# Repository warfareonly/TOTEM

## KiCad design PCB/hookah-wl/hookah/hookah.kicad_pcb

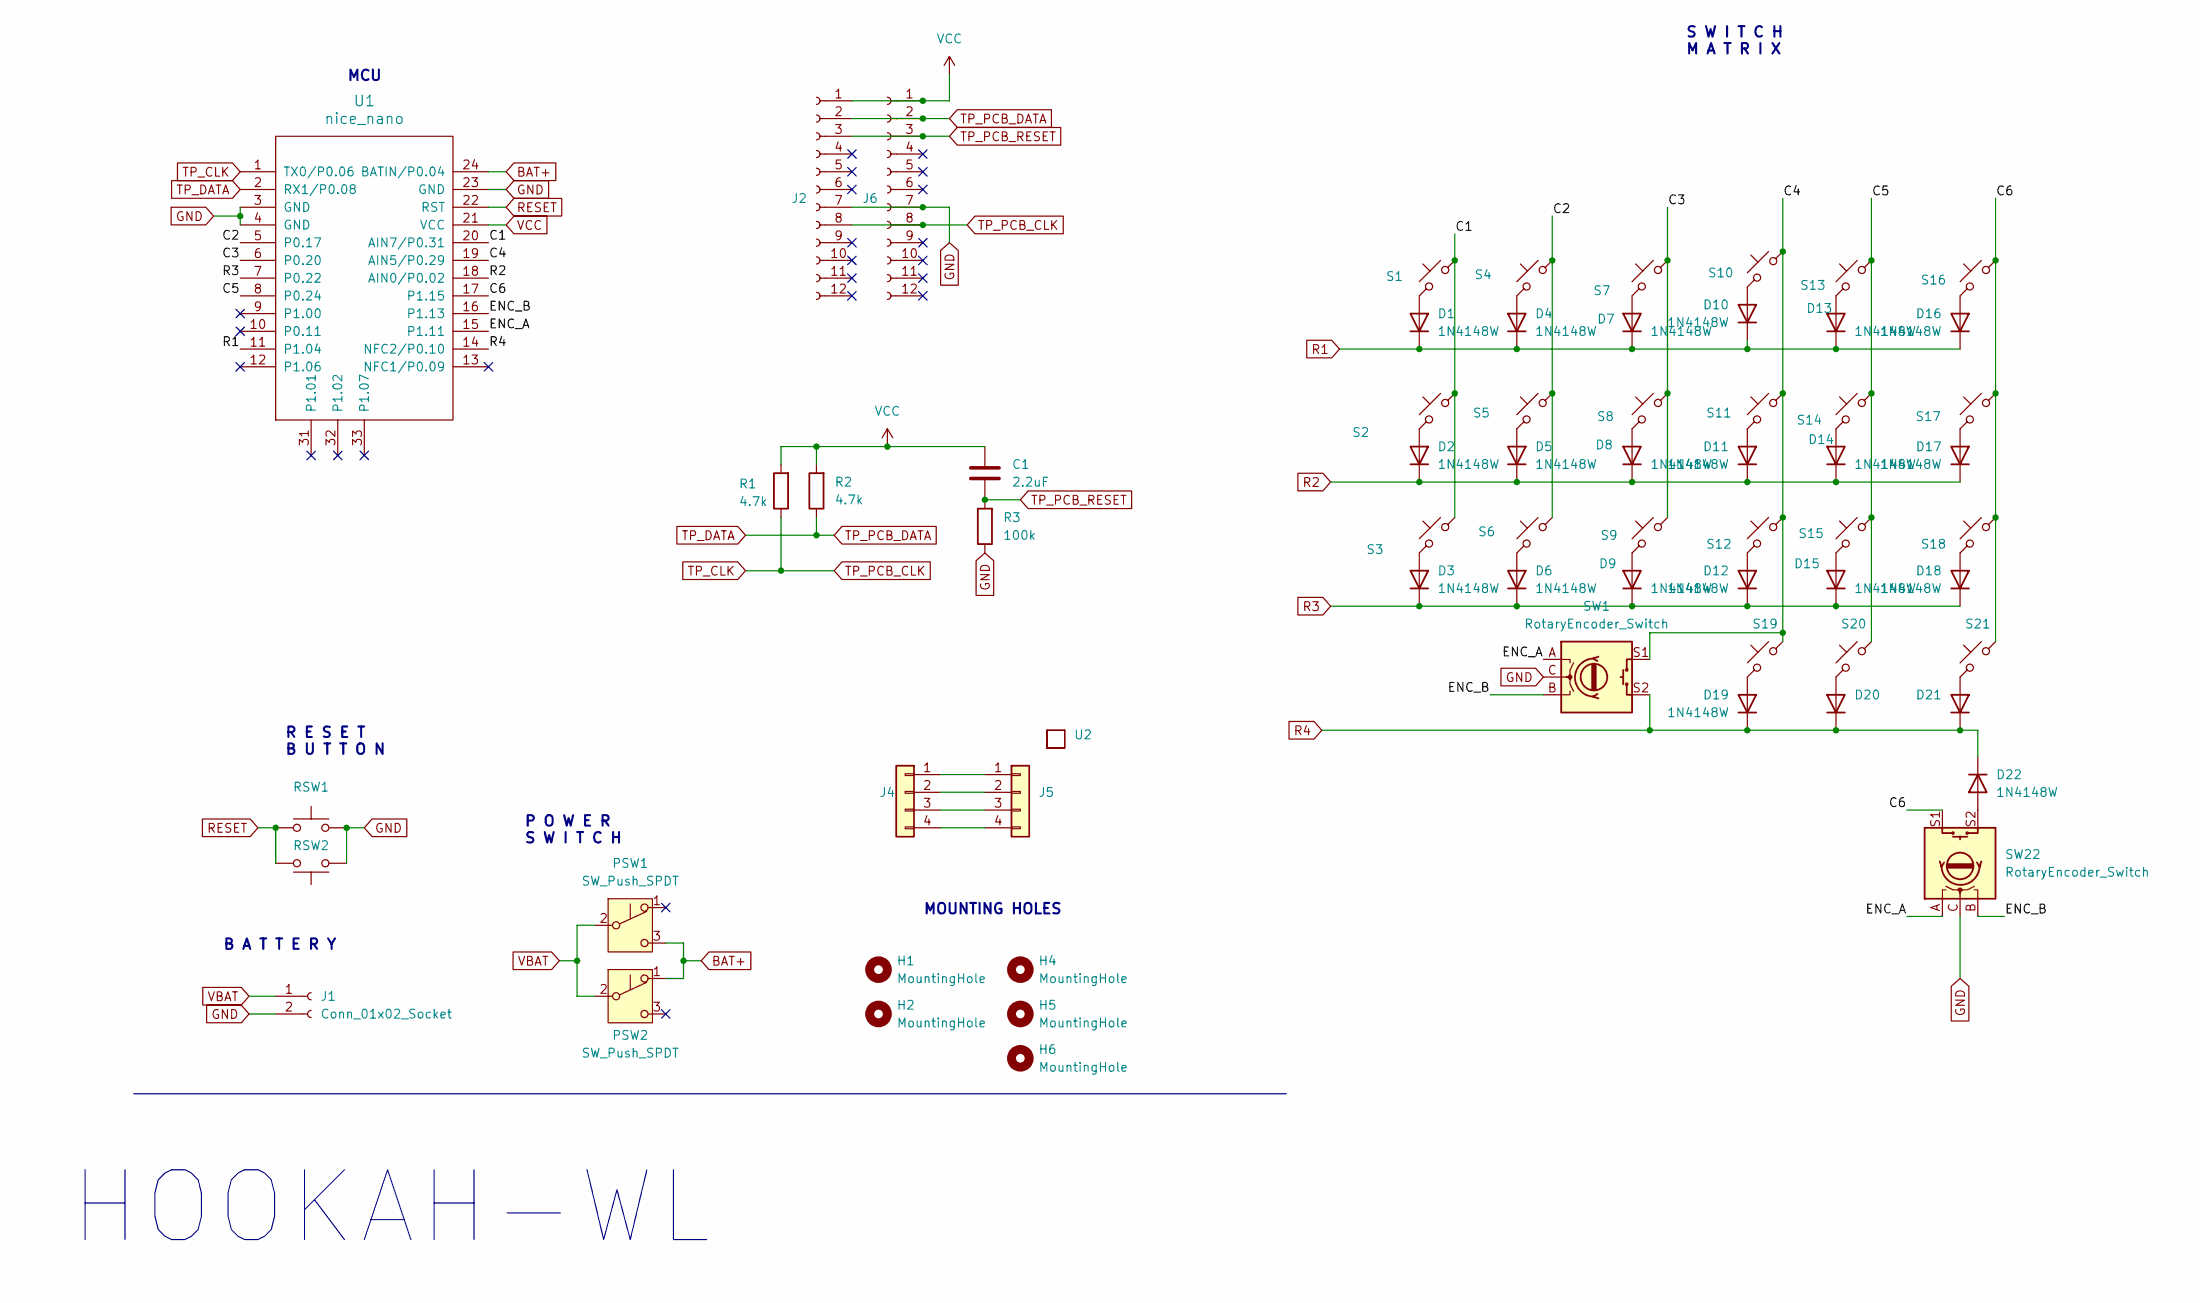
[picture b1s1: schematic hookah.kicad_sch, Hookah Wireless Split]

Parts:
C1: 2.2uF; C_0402_1005Metric_Pad0.74x0.62mm_HandSolder
D1, D2, D3, D4, D5, D6, D7, D8, D9, D10, D11, D12, D13, D14, D15, D16, D17, D18, D19, D20, D21, D22: 1N4148W; D_SOD-123_Reversible_THT
H1, H2, H4, H5, H6: MountingHole; M2-sandwich-hole
J1: Conn_01x02_Socket; JST_PH_S2B-PH-K_1x02_P2.00mm_Horizontal
J2, J6: Conn_01x12_Socket; Trackpoint_PCB_Connector
J4: Conn_01x04; TP_Conn_Sensor2PCB
J5: Conn_01x04; Trackpoint_Connector_Reversible
PSW1, PSW2: SW_Push_SPDT; switch-MSK-12C02-smd
R1, R2: 4.7k; R_0402_1005Metric_Pad0.72x0.64mm_HandSolder
R3: 100k; R_0402_1005Metric_Pad0.72x0.64mm_HandSolder
RSW1, RSW2: SW_Push; SW_SPST_B3U-1000P
S1, S2, S3, S4, S5, S6, S7, S8, S9, S10, S11, S12, S13, S14, S15, S16, S17, S18, S20, S21: SW_Push_45deg; wubbo-choc-socket-reversible
S19: SW_Push_45deg; SW_PG1350_reversible
SW1, SW22: RotaryEncoder_Switch; RotaryEncoder_Alps_EC11E-Switch_Vertical_H20mm
U1: nice_nano; ProMicro_unrouted_MAC8
U2: trackpoint_mount_t430

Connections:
/C1: S1.1, S2.1, S3.1, U1.20 (AIN7/P0.31)
/C2: S4.1, S5.1, S6.1, U1.5 (P0.17)
/C3: S7.1, S8.1, S9.1, U1.6 (P0.20)
/C4: S10.1, S11.1, S12.1, S19.1, SW1.S1, U1.19 (AIN5/P0.29)
/C5: S13.1, S14.1, S15.1, S20.1, U1.8 (P0.24)
/C6: S16.1, S17.1, S18.1, S21.1, SW22.S1, U1.17 (P1.15)
/ENC_A: SW1.A, SW22.A, U1.15 (P1.11)
/ENC_B: SW1.B, SW22.B, U1.16 (P1.13)
BAT+: PSW1.3 (C), PSW2.1 (A), U1.24 (BATIN/P0.04)
GND: J1.2, J2.7, J6.7, R3.1, RSW1.2, RSW2.1, SW1.C, SW22.C, U1.3 (GND), U1.4 (GND), U1.23 (GND)
unnamed: D1.2 (A), S1.2
unnamed: D2.2 (A), S2.2
unnamed: D3.2 (A), S3.2
unnamed: D4.2 (A), S4.2
unnamed: D5.2 (A), S5.2
unnamed: D6.2 (A), S6.2
unnamed: D7.2 (A), S7.2
unnamed: D8.2 (A), S8.2
unnamed: D9.2 (A), S9.2
unnamed: D10.2 (A), S10.2
unnamed: D11.2 (A), S11.2
unnamed: D12.2 (A), S12.2
unnamed: D13.2 (A), S13.2
unnamed: D14.2 (A), S14.2
unnamed: D15.2 (A), S15.2
unnamed: D16.2 (A), S16.2
unnamed: D17.2 (A), S17.2
unnamed: D18.2 (A), S18.2
unnamed: D19.2 (A), S19.2
unnamed: D20.2 (A), S20.2
unnamed: D21.2 (A), S21.2
unnamed: D22.2 (A), SW22.S2
unnamed: J4.1, J5.1
unnamed: J4.2, J5.2
unnamed: J4.3, J5.3
unnamed: J4.4, J5.4
R1: D1.1 (K), D4.1 (K), D7.1 (K), D10.1 (K), D13.1 (K), D16.1 (K), U1.11 (P1.04)
R2: D2.1 (K), D5.1 (K), D8.1 (K), D11.1 (K), D14.1 (K), D17.1 (K), U1.18 (AIN0/P0.02)
R3: D3.1 (K), D6.1 (K), D9.1 (K), D12.1 (K), D15.1 (K), D18.1 (K), U1.7 (P0.22)
R4: D19.1 (K), D20.1 (K), D21.1 (K), D22.1 (K), SW1.S2, U1.14 (NFC2/P0.10)
RESET: RSW1.1, RSW2.2, U1.22 (RST)
TP_CLK: J2.8, J6.8, R1.1, U1.1 (TX0/P0.06)
TP_DATA: J2.2, J6.2, R2.1, U1.2 (RX1/P0.08)
TP_PCB_RESET: C1.2, J2.3, J6.3, R3.2
VBAT: J1.1, PSW1.2 (B), PSW2.2 (B)
VCC: C1.1, J2.1, J6.1, R1.2, R2.2, U1.21 (VCC)

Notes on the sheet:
MOUNTING HOLES
R E S E T B U T T O N
S W I T C H M A T R I X
P O W E R S W I T C H
B A T T E R Y
MCU
HOOKAH-WL

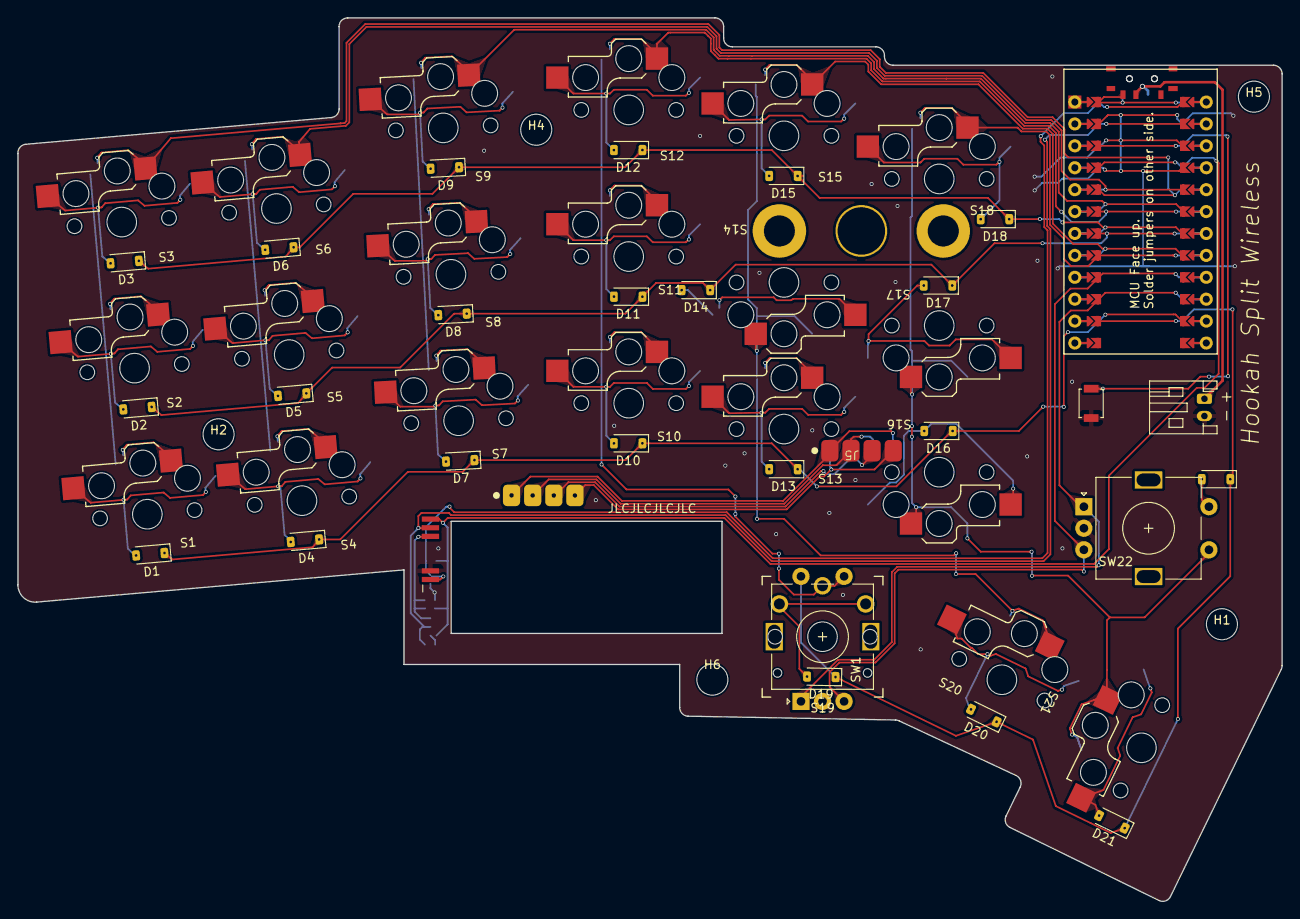
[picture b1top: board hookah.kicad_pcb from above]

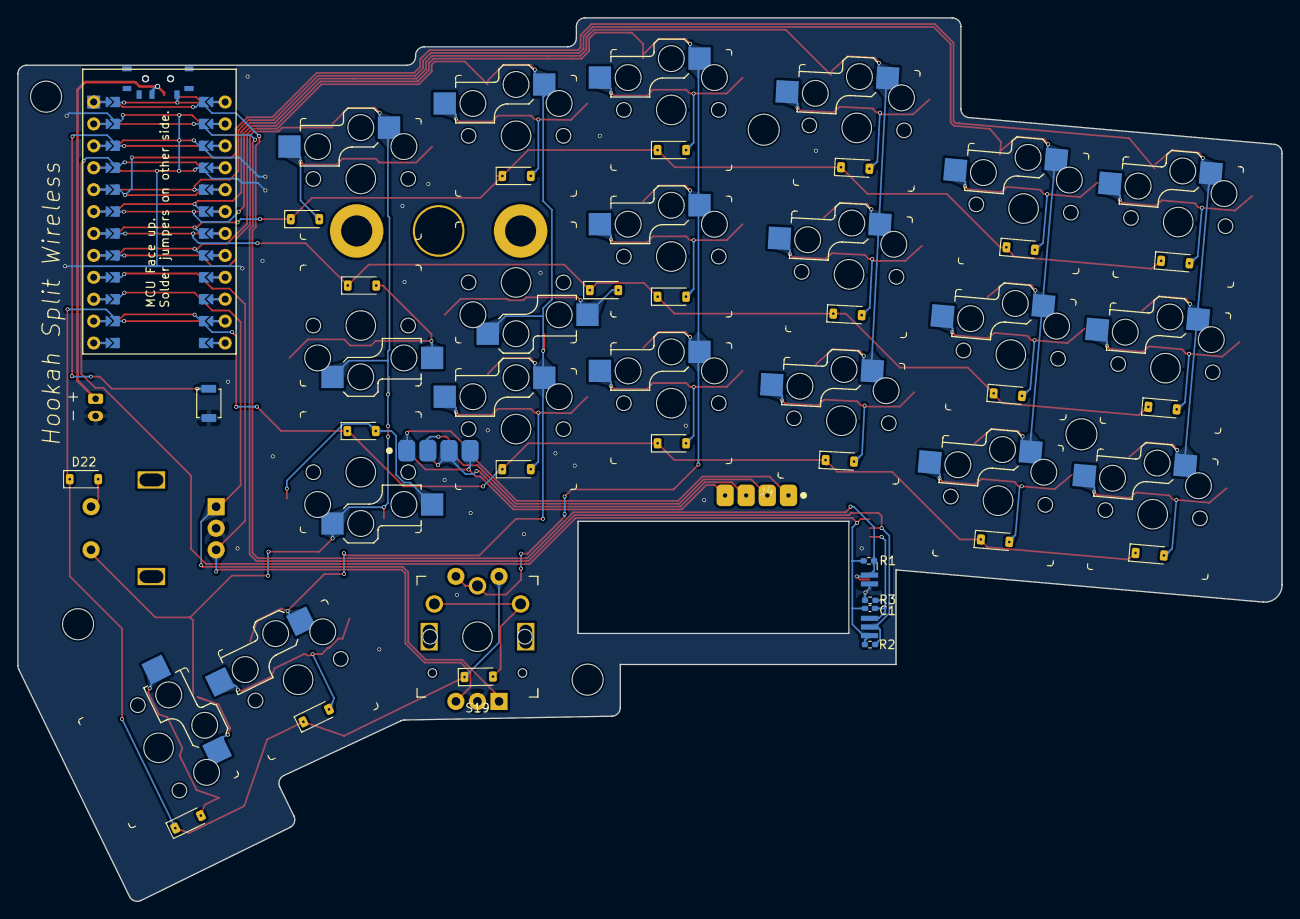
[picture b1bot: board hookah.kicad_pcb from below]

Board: 2 copper layers, 146.6 x 102.4 mm, 65 parts (9 on the bottom side), 46 nets.

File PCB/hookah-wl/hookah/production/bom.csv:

Designator,Footprint,Quantity,Value,LCSC Part #
C1,0402,1,2.2uF,
"D1, D10, D11, D12, D13, D14, D15, D16, D17, D18, D19, D2, D20, D21, D22, D3, D4, D5, D6, D7, D8, D9",D_SOD-123_Reversible_THT,22,1N4148W,
J1,JST_PH_S2B-PH-K_1x02_P2.00mm_Horizontal,1,Conn_01x02_Socket,
"J2, J6",Trackpoint_PCB_Connector,2,Conn_01x12_Socket,
J4,TP_Conn_Sensor2PCB,1,Conn_01x04,
J5,Trackpoint_Connector_Reversible,1,Conn_01x04,
"PSW1, PSW2",switch-MSK-12C02-smd,2,SW_Push_SPDT,
"R1, R2",0402,2,4.7k,
R3,0402,1,100k,
"RSW1, RSW2",SW_SPST_B3U-1000P,2,SW_Push,
"S1, S10, S11, S12, S13, S14, S15, S16, S17, S18, S2, S20, S21, S3, S4, S5, S6, S7, S8, S9",wubbo-choc-socket-reversible,20,SW_Push_45deg,
S19,SW_PG1350_reversible,1,SW_Push_45deg,
"SW1, SW22",RotaryEncoder_Alps_EC11E-Switch_Vertical_H20mm,2,RotaryEncoder_Switch,
U1,ProMicro_unrouted_MAC8,1,nice_nano,
U2,trackpoint_mount_t430,1,~,

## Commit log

2024-08-05 Add teardrops and fix some traces
2024-08-10 Modded for nice-nano
2024-09-28 n!n version
2024-10-08 Hookah WL final
